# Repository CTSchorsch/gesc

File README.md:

# gesc
DC Motor Controler based on Benjamin Vedders VESC(TM)

Round shape, fits into a DPV tube.
48V (13s), max 60A, needs cooling

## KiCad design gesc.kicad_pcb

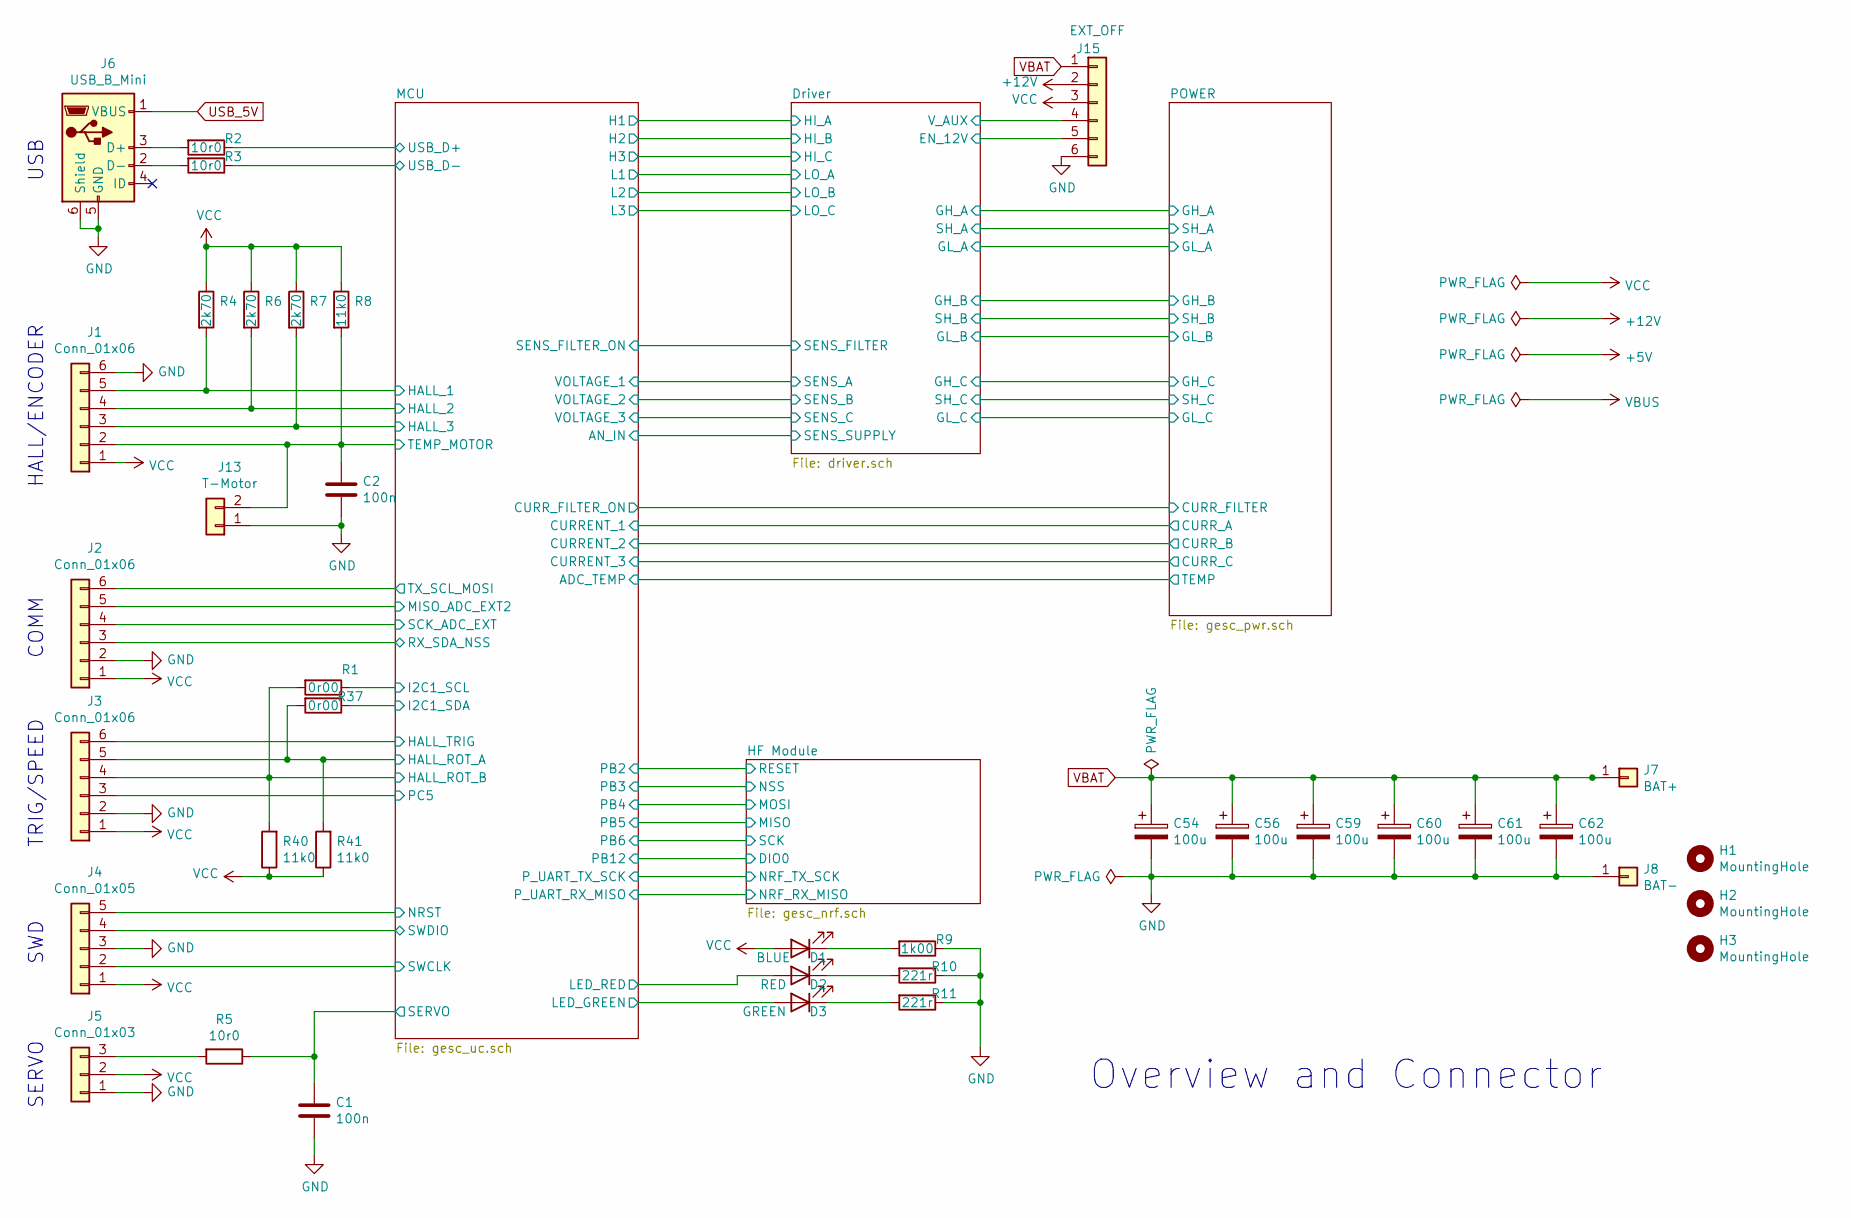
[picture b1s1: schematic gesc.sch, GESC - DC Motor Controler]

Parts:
C1, C2: 100n; C_0805_2012Metric
C54, C56, C59, C60, C61, C62: 100u; CP_Elec_10x10
D1: BLUE; LED_0805_2012Metric
D2: RED; LED_0805_2012Metric
D3: GREEN; LED_0805_2012Metric
H1, H2, H3: MountingHole; MountingHole_3.2mm_M3
J1, J2, J3: Conn_01x06; JST_SH_BM06B-SRSS-TB_1x06-1MP_P1.00mm_Vertical
J4: Conn_01x05; PinHeader_1x05_P2.54mm_Vertical
J5: Conn_01x03; JST_SH_BM03B-SRSS-TB_1x03-1MP_P1.00mm_Vertical
J6: USB_B_Mini; USB_Micro-B_Wuerth_614105150721_Vertical_CircularHoles
J7: BAT+; TestPoint_Pad_5.0x5.0mm
J8: BAT-; TestPoint_Pad_5.0x5.0mm
J13: T-Motor; JST_SH_BM02B-SRSS-TB_1x02-1MP_P1.00mm_Vertical
J15: EXT_OFF; JST_SH_BM06B-SRSS-TB_1x06-1MP_P1.00mm_Vertical
R1, R37: 0r00; R_0805_2012Metric
R2, R3, R5: 10r0; R_0805_2012Metric
R4: 2k70; R_0805_2012Metric; LCSC 1
R6, R7: 2k70; R_0805_2012Metric
R8, R40, R41: 11k0; R_0805_2012Metric
R9: 1k00; R_0805_2012Metric
R10, R11: 221r; R_0805_2012Metric

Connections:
+12V: J15.2; also elsewhere on the board
/Driver/EN_12V: J15.5; also elsewhere on the board
/Driver/V_AUX: J15.4; also elsewhere on the board
/MCU/HALL_1: J1.5, R4.2; also elsewhere on the board
/MCU/HALL_2: J1.4, R6.2; also elsewhere on the board
/MCU/HALL_3: J1.3, R7.2; also elsewhere on the board
/MCU/HALL_ROT_A: J3.5, R37.2, R41.2; also elsewhere on the board
/MCU/HALL_ROT_B: J3.4, R1.2, R40.2; also elsewhere on the board
/MCU/HALL_TRIG: J3.6; also elsewhere on the board
/MCU/I2C1_SCL: R1.1; also elsewhere on the board
/MCU/I2C1_SDA: R37.1; also elsewhere on the board
/MCU/LED_GREEN: D3.2 (A); also elsewhere on the board
/MCU/LED_RED: D2.2 (A); also elsewhere on the board
/MCU/MISO_ADC_EXT2: J2.5; also elsewhere on the board
/MCU/NRST: J4.5; also elsewhere on the board
/MCU/PC5: J3.3; also elsewhere on the board
/MCU/RX_SDA_NSS: J2.3; also elsewhere on the board
/MCU/SCK_ADC_EXT: J2.4; also elsewhere on the board
/MCU/SERVO: C1.1, R5.1; also elsewhere on the board
/MCU/SWCLK: J4.2; also elsewhere on the board
/MCU/SWDIO: J4.4; also elsewhere on the board
/MCU/TEMP_MOTOR: C2.1, J1.2, J13.2, R8.2; also elsewhere on the board
/MCU/TX_SCL_MOSI: J2.6; also elsewhere on the board
/MCU/USB_D+: R2.1; also elsewhere on the board
/MCU/USB_D-: R3.1; also elsewhere on the board
GND: C1.2, C2.2, C54.2, C56.2, C59.2, C60.2, C61.2, C62.2, J1.6, J2.2, J3.2, J4.3, J5.1, J6.5 (GND), J6.6 (Shield), J8.1, J13.1, J15.6, R9.1, R10.1, R11.1; also elsewhere on the board
unnamed: D1.1 (K), R9.2
unnamed: D2.1 (K), R10.2
unnamed: D3.1 (K), R11.2
unnamed: J5.3, R5.2
unnamed: J6.2 (D-), R3.2
unnamed: J6.3 (D+), R2.2
USB_5V: J6.1 (VBUS); also elsewhere on the board
VBAT: C54.1, C56.1, C59.1, C60.1, C61.1, C62.1, J7.1, J15.1; also elsewhere on the board
VCC: D1.2 (A), J1.1, J2.1, J3.1, J4.1, J5.2, J15.3, R4.1, R6.1, R7.1, R8.1, R40.1, R41.1; also elsewhere on the board

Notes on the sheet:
Overview and Connector
USB
HALL/ENCODER
COMM
TRIG/SPEED
SWD
SERVO

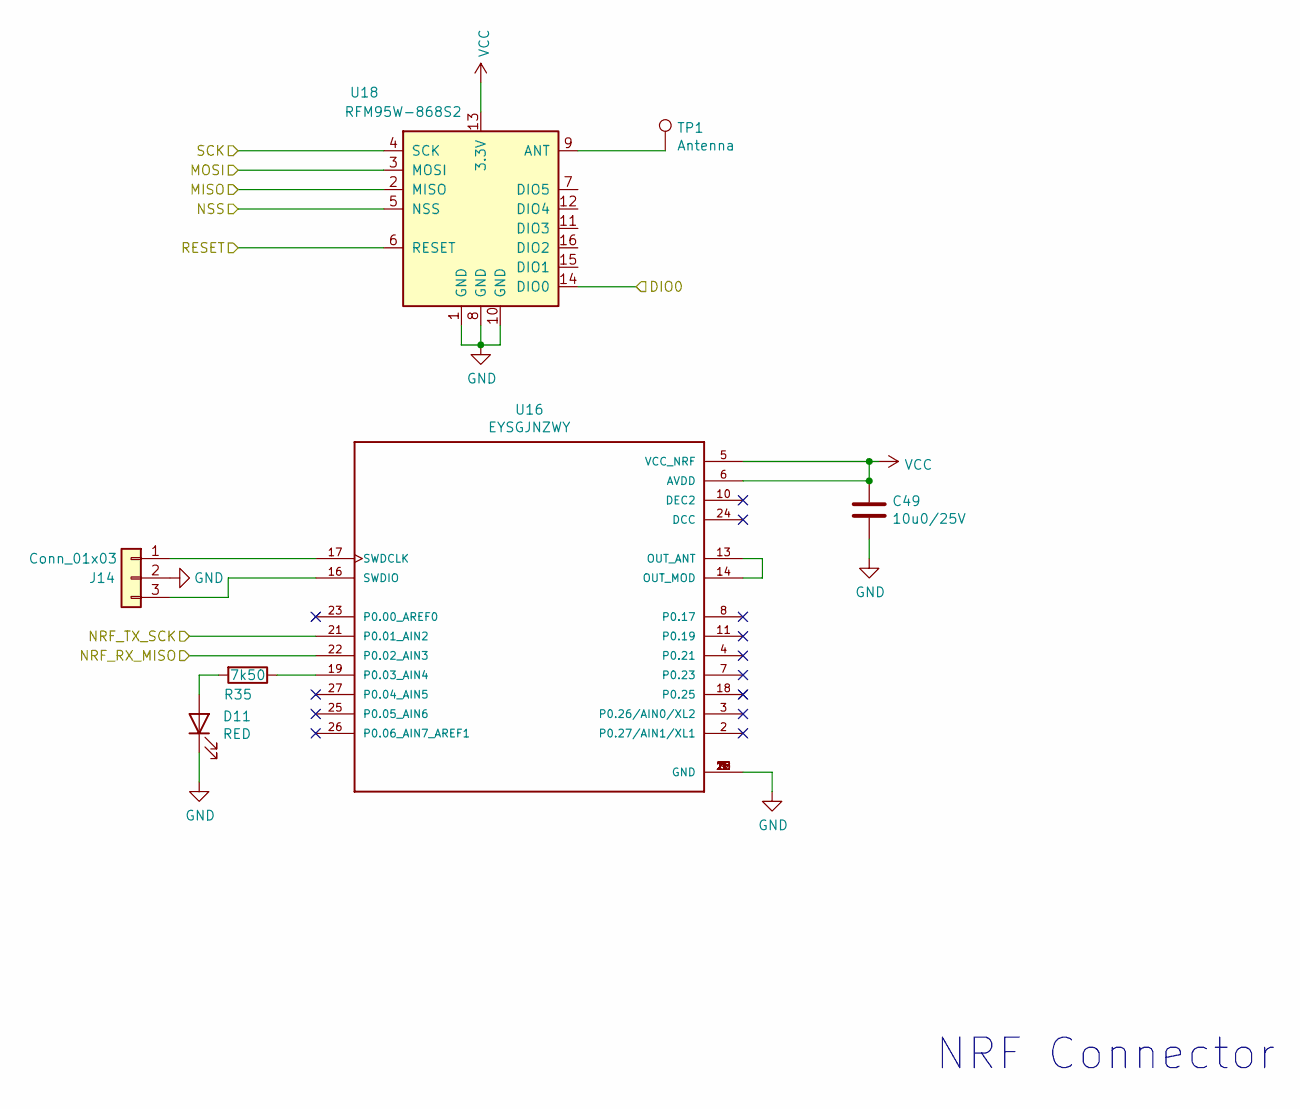
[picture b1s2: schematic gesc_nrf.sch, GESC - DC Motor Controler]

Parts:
C49: 10u0/25V; C_0805_2012Metric
D11: RED; LED_0805_2012Metric
J14: Conn_01x03; PinHeader_1x03_P2.54mm_Vertical
R35: 7k50; R_0805_2012Metric
TP1: Antenna; TestPoint_Pad_D2.0mm
U16: EYSGJNZWY; BLE_EYSGJNZWY
U18: RFM95W-868S2; XCVR_RFM95W-868S2

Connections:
/HF Module/DIO0: U18.14 (DIO0); also elsewhere on the board
/HF Module/MISO: U18.2 (MISO); also elsewhere on the board
/HF Module/MOSI: U18.3 (MOSI); also elsewhere on the board
/HF Module/NRF_RX_MISO: U16.22 (P0.02_AIN3); also elsewhere on the board
/HF Module/NRF_TX_SCK: U16.21 (P0.01_AIN2); also elsewhere on the board
/HF Module/NSS: U18.5 (NSS); also elsewhere on the board
/MCU/PB2: U18.6 (RESET); also elsewhere on the board
/MCU/PB6: U18.4 (SCK); also elsewhere on the board
GND: C49.2, D11.1 (K), J14.2, U16.1 (GND), U16.9 (GND), U16.12 (GND), U16.15 (GND), U16.20 (GND), U16.28 (GND), U18.1 (GND), U18.8 (GND), U18.10 (GND); also elsewhere on the board
unnamed: D11.2 (A), R35.2
unnamed: J14.1, U16.17 (SWDCLK)
unnamed: J14.3, U16.16 (SWDIO)
unnamed: R35.1, U16.19 (P0.03_AIN4)
unnamed 102: TP1.1, U18.9 (ANT); also elsewhere on the board
unnamed: U16.13 (OUT_ANT), U16.14 (OUT_MOD)
VCC: C49.1, U16.5 (VCC_NRF), U16.6 (AVDD), U18.13 (3.3V); also elsewhere on the board

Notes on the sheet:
NRF Connector

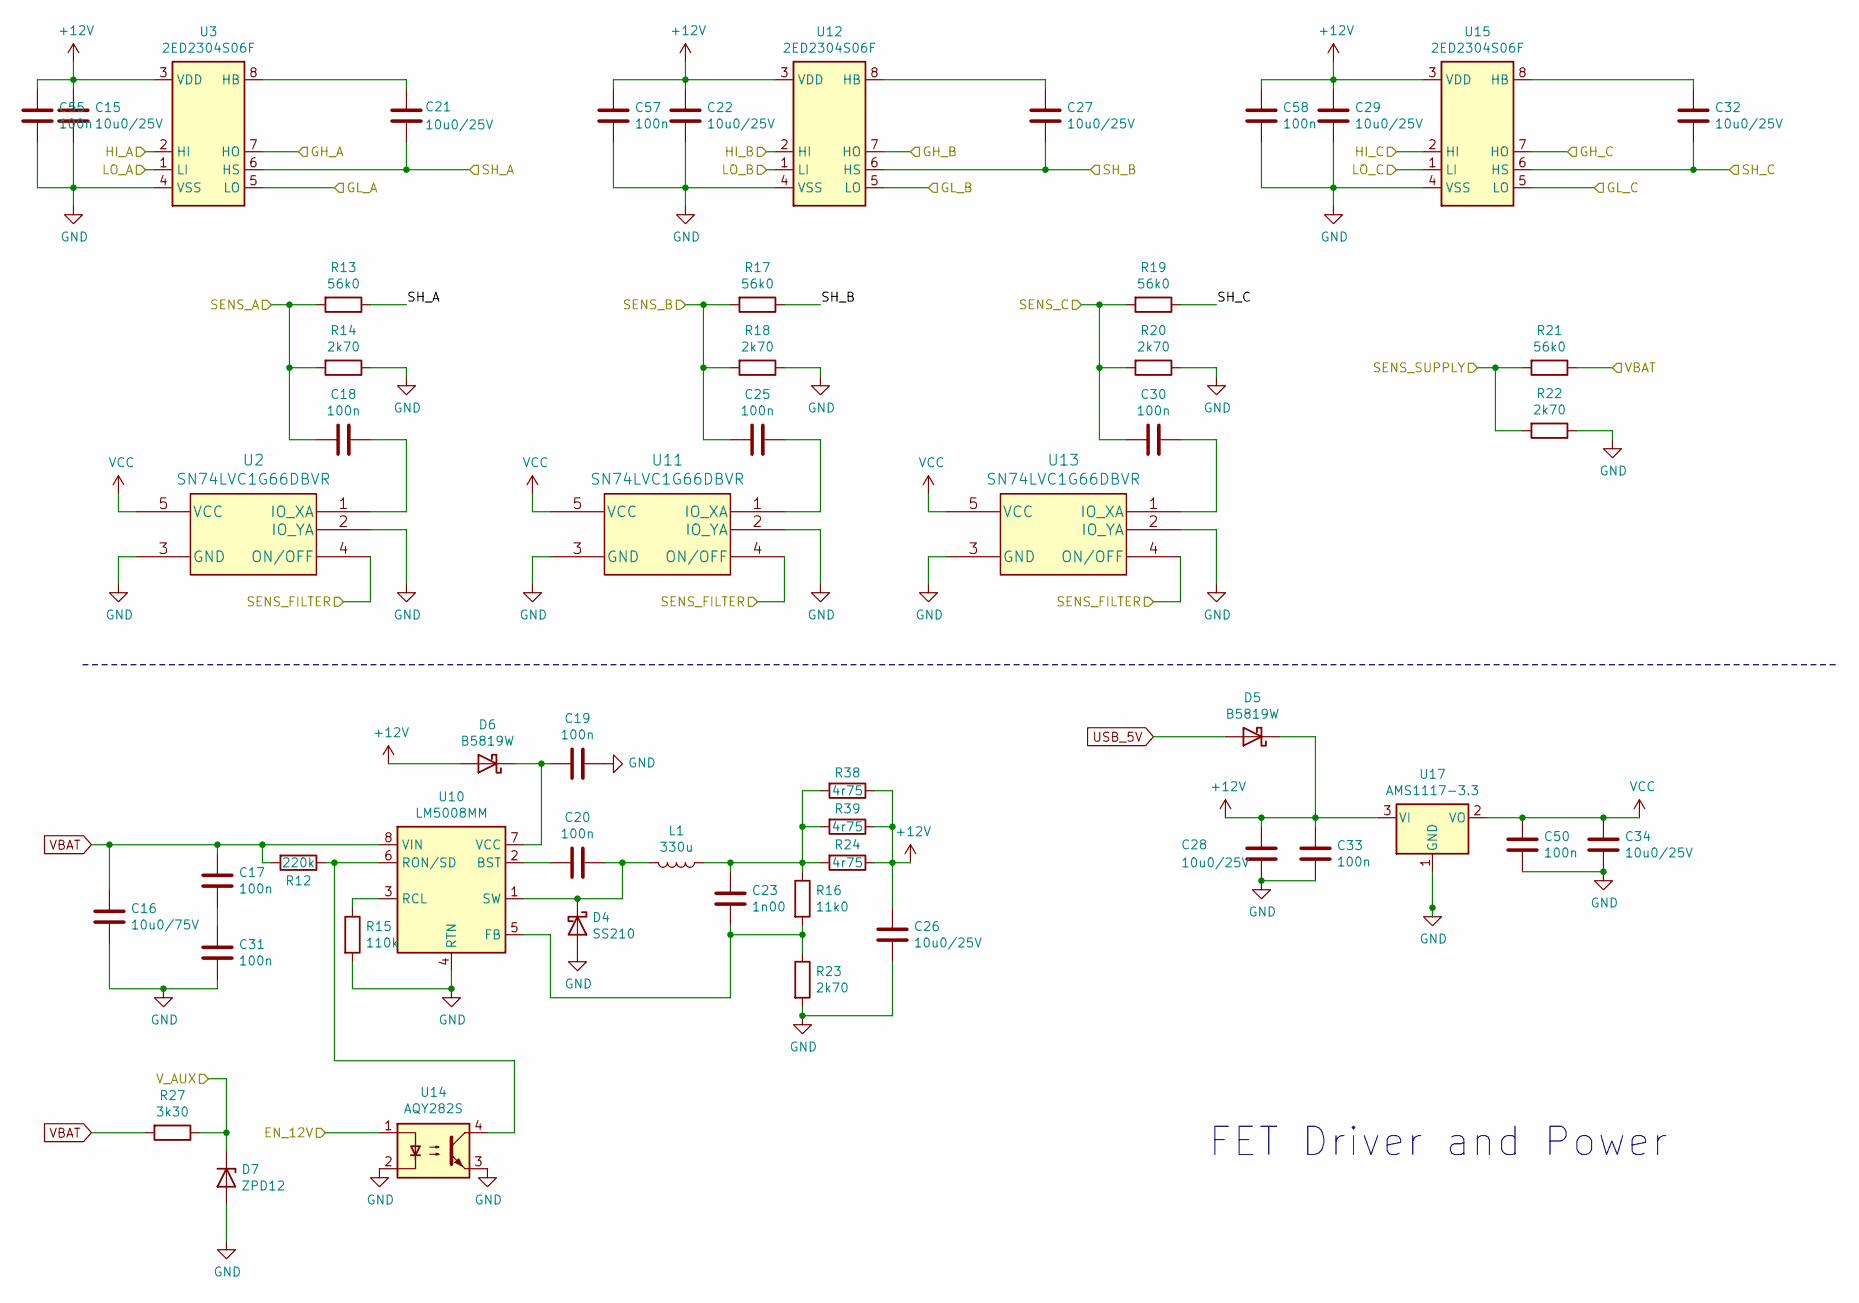
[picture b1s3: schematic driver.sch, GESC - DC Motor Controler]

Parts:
C15, C21, C22, C26, C27, C28, C29, C32, C34: 10u0/25V; C_0805_2012Metric
C16: 10u0/75V; C_1210_3225Metric
C17, C18, C19, C20, C25, C30, C31, C33, C50, C55, C57, C58: 100n; C_0805_2012Metric
C23: 1n00; C_0805_2012Metric
D4: SS210; D_SMA; LCSC C14996
D5, D6: B5819W; D_SOD-123; LCSC C8598
D7: ZPD12; D_MiniMELF
L1: 330u; L_6.3x6.3_H3; Partnumber SWPA6045S331MT; LCSC C83453
R12: 220k; R_0805_2012Metric
R13, R17, R19, R21: 56k0; R_0805_2012Metric
R14, R18, R20, R22, R23: 2k70; R_0805_2012Metric
R15: 110k; R_0805_2012Metric
R16: 11k0; R_0805_2012Metric
R24, R38, R39: 4r75; R_0805_2012Metric
R27: 3k30; R_0805_2012Metric
U2, U11, U13: SN74LVC1G66DBVR; M74VHC1GT66DTT1G; LCSC C133643
U3, U12, U15: 2ED2304S06F; SOIC-8_3.9x4.9mm_P1.27mm
U10: LM5008MM; MSOP-8_3x3mm_P0.65mm; LCSC C9424
U14: AQY282S; SO-4_4.4x4.3mm_P2.54mm; LCSC C250827
U17: AMS1117-3.3; SOT-223-3_TabPin2

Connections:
+12V: C15.1, C22.1, C26.1, C28.1, C29.1, C33.1, C55.1, C57.1, C58.1, D5.1 (K), D6.2 (A), R24.1, R38.1, R39.1, U3.3 (VDD), U12.3 (VDD), U15.3 (VDD), U17.3 (VI); also elsewhere on the board
/Driver/EN_12V: U14.1; also elsewhere on the board
/Driver/GH_A: U3.7 (HO); also elsewhere on the board
/Driver/GH_B: U12.7 (HO); also elsewhere on the board
/Driver/GH_C: U15.7 (HO); also elsewhere on the board
/Driver/GL_A: U3.5 (LO); also elsewhere on the board
/Driver/GL_B: U12.5 (LO); also elsewhere on the board
/Driver/GL_C: U15.5 (LO); also elsewhere on the board
/Driver/SENS_A: C18.2, R13.2, R14.2; also elsewhere on the board
/Driver/SENS_B: C25.2, R17.2, R18.2; also elsewhere on the board
/Driver/SENS_C: C30.2, R19.2, R20.2; also elsewhere on the board
/Driver/SENS_FILTER: U2.4 (ON/OFF), U11.4 (ON/OFF), U13.4 (ON/OFF); also elsewhere on the board
/Driver/SH_A: C21.2, R13.1, U3.6 (HS); also elsewhere on the board
/Driver/SH_B: C27.2, R17.1, U12.6 (HS); also elsewhere on the board
/Driver/SH_C: C32.2, R19.1, U15.6 (HS); also elsewhere on the board
/Driver/V_AUX: D7.1 (K), R27.1; also elsewhere on the board
/MCU/AN_IN: R21.2, R22.2; also elsewhere on the board
/MCU/H1: U3.2 (HI); also elsewhere on the board
/MCU/H2: U12.2 (HI); also elsewhere on the board
/MCU/H3: U15.2 (HI); also elsewhere on the board
/MCU/L1: U3.1 (LI); also elsewhere on the board
/MCU/L2: U12.1 (LI); also elsewhere on the board
/MCU/L3: U15.1 (LI); also elsewhere on the board
GND: C15.2, C16.2, C19.2, C22.2, C26.2, C28.2, C29.2, C31.2, C33.2, C34.2, C50.2, C55.2, C57.2, C58.2, D4.2 (A), D7.2 (A), R14.1, R15.2, R18.1, R20.1, R22.1, R23.2, U2.2 (IO_YA), U2.3 (GND), U3.4 (VSS), U10.4 (RTN), U11.2 (IO_YA), U11.3 (GND), U12.4 (VSS), U13.2 (IO_YA), U13.3 (GND), U14.2, U14.3, U15.4 (VSS), U17.1 (GND); also elsewhere on the board
unnamed: C17.2, C31.1
unnamed: C18.1, U2.1 (IO_XA)
unnamed: C19.1, D6.1 (K), U10.7 (VCC)
unnamed: C20.1, U10.2 (BST)
unnamed: C20.2, D4.1 (K), L1.2, U10.1 (SW)
unnamed: C21.1, U3.8 (HB)
unnamed: C23.1, L1.1, R16.1, R24.2, R38.2, R39.2
unnamed: C23.2, R16.2, R23.1, U10.5 (FB)
unnamed: C25.1, U11.1 (IO_XA)
unnamed: C27.1, U12.8 (HB)
unnamed: C30.1, U13.1 (IO_XA)
unnamed: C32.1, U15.8 (HB)
unnamed: R12.1, U10.6 (RON/SD), U14.4
unnamed: R15.1, U10.3 (RCL)
USB_5V: D5.2 (A); also elsewhere on the board
VBAT: C16.1, C17.1, R12.2, R21.1, R27.2, U10.8 (VIN); also elsewhere on the board
VCC: C34.1, C50.1, U2.5 (VCC), U11.5 (VCC), U13.5 (VCC), U17.2 (VO); also elsewhere on the board

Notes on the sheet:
FET Driver and Power

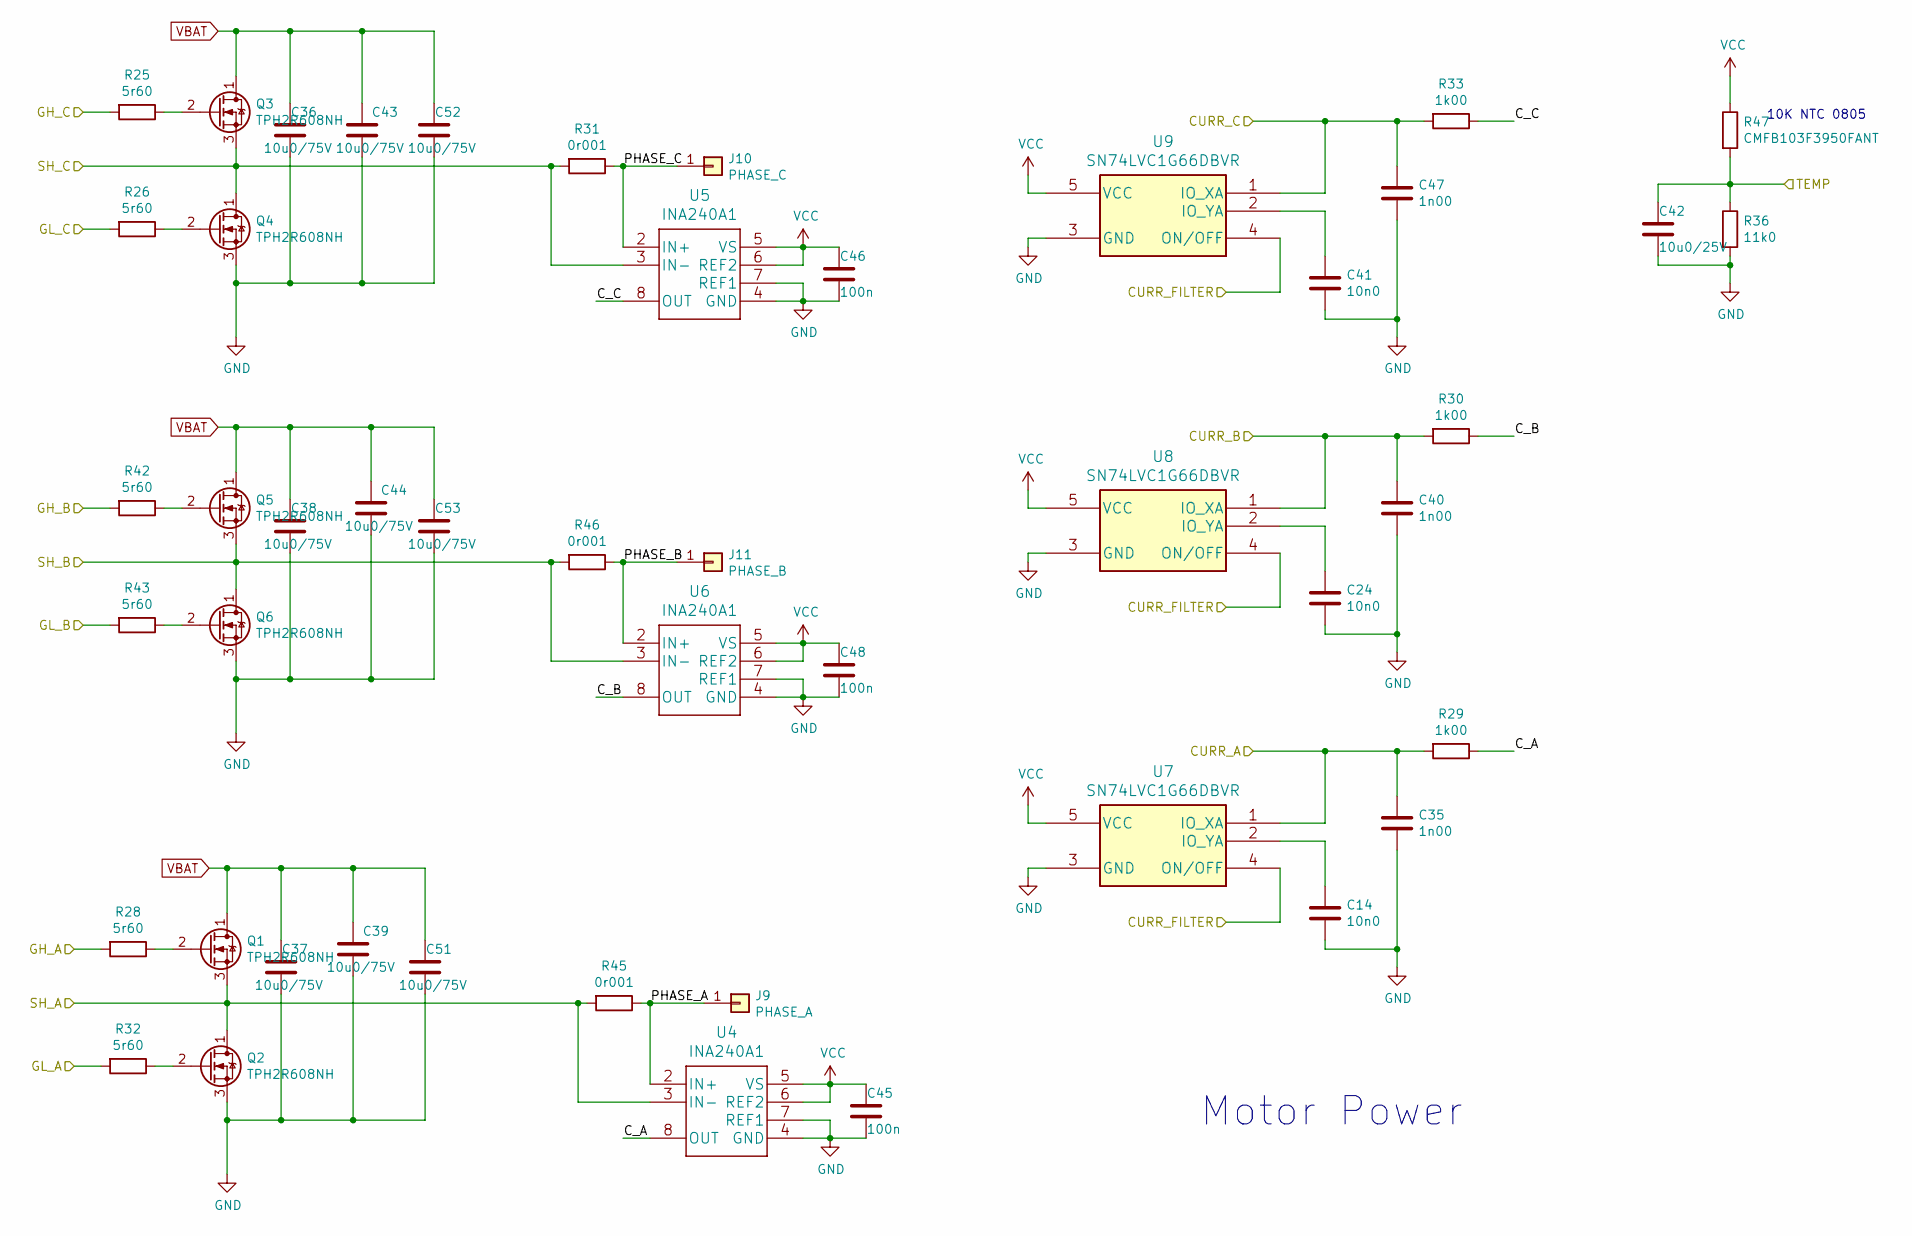
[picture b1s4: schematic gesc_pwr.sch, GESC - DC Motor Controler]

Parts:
C14, C24, C41: 10n0; C_0805_2012Metric
C35, C40, C47: 1n00; C_0805_2012Metric
C36: 10u0/75V; C_1210_3225Metric; LCSC C15850
C37, C38, C39, C43, C44, C51, C52, C53: 10u0/75V; C_1210_3225Metric
C42: 10u0/25V; C_0805_2012Metric
C45, C46, C48: 100n; C_0805_2012Metric
J9: PHASE_A; TestPoint_Pad_5.0x5.0mm
J10: PHASE_C; TestPoint_Pad_5.0x5.0mm
J11: PHASE_B; TestPoint_Pad_5.0x5.0mm
Q1, Q2, Q3, Q4, Q5, Q6: TPH2R608NH; TRANS_TPHR8504PL-3PIN; Partnumber TPH2R608NH; LCSC C146377
R25, R26, R28, R32, R42, R43: 5r60; R_0805_2012Metric
R29, R30, R33: 1k00; R_0805_2012Metric
R31, R45, R46: 0r001; R_2512_6332Metric
R36: 11k0; R_0805_2012Metric
R47: CMFB103F3950FANT; R_0805_2012Metric
U4, U5, U6: INA240A1; INA240A1QPWRQ1; LCSC C93965
U7, U8, U9: SN74LVC1G66DBVR; M74VHC1GT66DTT1G; LCSC C133643

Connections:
/Driver/GH_A: R28.2; also elsewhere on the board
/Driver/GH_B: R42.2; also elsewhere on the board
/Driver/GH_C: R25.2; also elsewhere on the board
/Driver/GL_A: R32.2; also elsewhere on the board
/Driver/GL_B: R43.2; also elsewhere on the board
/Driver/GL_C: R26.2; also elsewhere on the board
/Driver/SH_A: Q1.3 (S), Q2.1 (D), R45.2, U4.3 (IN-); also elsewhere on the board
/Driver/SH_B: Q5.3 (S), Q6.1 (D), R46.2, U6.3 (IN-); also elsewhere on the board
/Driver/SH_C: Q3.3 (S), Q4.1 (D), R31.2, U5.3 (IN-); also elsewhere on the board
/MCU/ADC_TEMP: C42.1, R36.1, R47.2; also elsewhere on the board
/MCU/CURRENT_1: C35.1, R29.2, U7.1 (IO_XA); also elsewhere on the board
/MCU/CURRENT_2: C40.1, R30.2, U8.1 (IO_XA); also elsewhere on the board
/MCU/CURRENT_3: C47.1, R33.2, U9.1 (IO_XA); also elsewhere on the board
/POWER/CURR_FILTER: U7.4 (ON/OFF), U8.4 (ON/OFF), U9.4 (ON/OFF); also elsewhere on the board
/POWER/C_A: R29.1, U4.8 (OUT)
/POWER/C_B: R30.1, U6.8 (OUT)
/POWER/C_C: R33.1, U5.8 (OUT)
/POWER/PHASE_A: J9.1, R45.1, U4.2 (IN+)
/POWER/PHASE_B: J11.1, R46.1, U6.2 (IN+)
/POWER/PHASE_C: J10.1, R31.1, U5.2 (IN+)
GND: C14.2, C24.2, C35.2, C36.2, C37.2, C38.2, C39.2, C40.2, C41.2, C42.2, C43.2, C44.2, C45.2, C46.2, C47.2, C48.2, C51.2, C52.2, C53.2, Q2.3 (S), Q4.3 (S), Q6.3 (S), R36.2, U4.4 (GND), U4.7 (REF1), U5.4 (GND), U5.7 (REF1), U6.4 (GND), U6.7 (REF1), U7.3 (GND), U8.3 (GND), U9.3 (GND); also elsewhere on the board
unnamed: C14.1, U7.2 (IO_YA)
unnamed: C24.1, U8.2 (IO_YA)
unnamed: C41.1, U9.2 (IO_YA)
unnamed: Q1.2 (G), R28.1
unnamed: Q2.2 (G), R32.1
unnamed: Q3.2 (G), R25.1
unnamed: Q4.2 (G), R26.1
unnamed: Q5.2 (G), R42.1
unnamed: Q6.2 (G), R43.1
VBAT: C36.1, C37.1, C38.1, C39.1, C43.1, C44.1, C51.1, C52.1, C53.1, Q1.1 (D), Q3.1 (D), Q5.1 (D); also elsewhere on the board
VCC: C45.1, C46.1, C48.1, R47.1, U4.5 (VS), U4.6 (REF2), U5.5 (VS), U5.6 (REF2), U6.5 (VS), U6.6 (REF2), U7.5 (VCC), U8.5 (VCC), U9.5 (VCC); also elsewhere on the board

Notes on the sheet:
Motor Power
10K NTC 0805

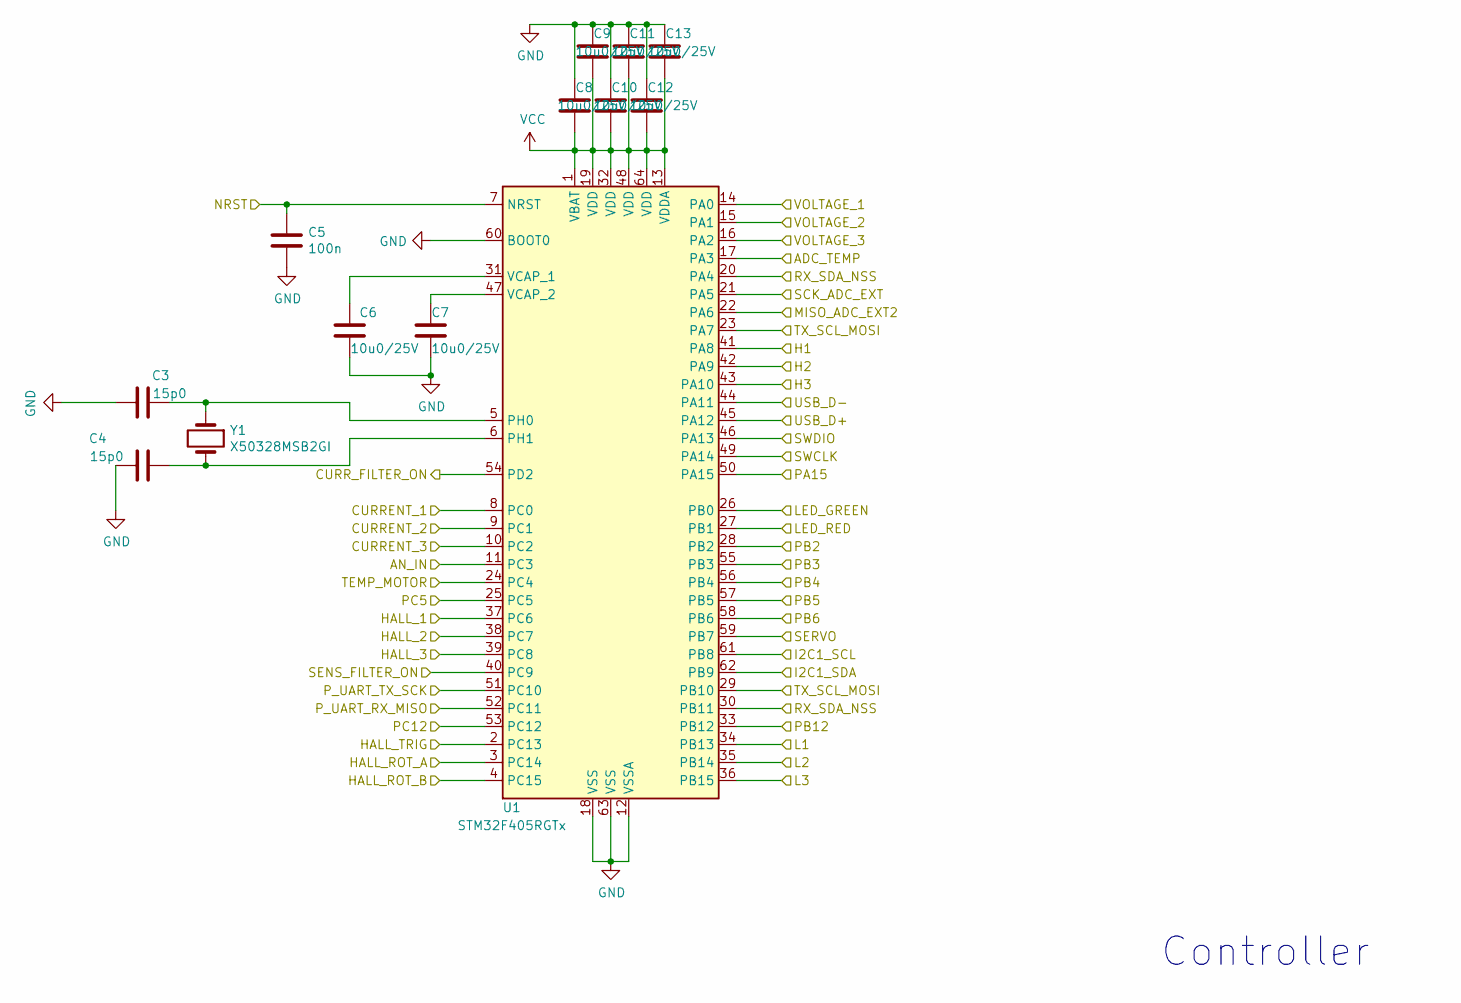
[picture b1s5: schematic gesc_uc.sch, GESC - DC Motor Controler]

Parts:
C3, C4: 15p0; C_0805_2012Metric
C5: 100n; C_0805_2012Metric
C6, C7, C8, C9, C10, C11, C12, C13: 10u0/25V; C_0805_2012Metric
U1: STM32F405RGTx; LQFP-64_10x10mm_P0.5mm; LCSC C15742
Y1: X50328MSB2GI; Crystal_SMD_5032-2Pin_5.0x3.2mm; LCSC C115962

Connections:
/Driver/SENS_A: U1.14 (PA0); also elsewhere on the board
/Driver/SENS_B: U1.15 (PA1); also elsewhere on the board
/Driver/SENS_C: U1.16 (PA2); also elsewhere on the board
/Driver/SENS_FILTER: U1.40 (PC9); also elsewhere on the board
/HF Module/DIO0: U1.33 (PB12); also elsewhere on the board
/HF Module/MISO: U1.57 (PB5); also elsewhere on the board
/HF Module/MOSI: U1.56 (PB4); also elsewhere on the board
/HF Module/NRF_RX_MISO: U1.52 (PC11); also elsewhere on the board
/HF Module/NRF_TX_SCK: U1.51 (PC10); also elsewhere on the board
/HF Module/NSS: U1.55 (PB3); also elsewhere on the board
/MCU/ADC_TEMP: U1.17 (PA3); also elsewhere on the board
/MCU/AN_IN: U1.11 (PC3); also elsewhere on the board
/MCU/CURRENT_1: U1.8 (PC0); also elsewhere on the board
/MCU/CURRENT_2: U1.9 (PC1); also elsewhere on the board
/MCU/CURRENT_3: U1.10 (PC2); also elsewhere on the board
/MCU/H1: U1.41 (PA8); also elsewhere on the board
/MCU/H2: U1.42 (PA9); also elsewhere on the board
/MCU/H3: U1.43 (PA10); also elsewhere on the board
/MCU/HALL_1: U1.37 (PC6); also elsewhere on the board
/MCU/HALL_2: U1.38 (PC7); also elsewhere on the board
/MCU/HALL_3: U1.39 (PC8); also elsewhere on the board
/MCU/HALL_ROT_A: U1.3 (PC14); also elsewhere on the board
/MCU/HALL_ROT_B: U1.4 (PC15); also elsewhere on the board
/MCU/HALL_TRIG: U1.2 (PC13); also elsewhere on the board
/MCU/I2C1_SCL: U1.61 (PB8); also elsewhere on the board
/MCU/I2C1_SDA: U1.62 (PB9); also elsewhere on the board
/MCU/L1: U1.34 (PB13); also elsewhere on the board
/MCU/L2: U1.35 (PB14); also elsewhere on the board
/MCU/L3: U1.36 (PB15); also elsewhere on the board
/MCU/LED_GREEN: U1.26 (PB0); also elsewhere on the board
/MCU/LED_RED: U1.27 (PB1); also elsewhere on the board
/MCU/MISO_ADC_EXT2: U1.22 (PA6); also elsewhere on the board
/MCU/NRST: C5.1, U1.7 (NRST); also elsewhere on the board
/MCU/PB2: U1.28 (PB2); also elsewhere on the board
/MCU/PB6: U1.58 (PB6); also elsewhere on the board
/MCU/PC5: U1.25 (PC5); also elsewhere on the board
/MCU/RX_SDA_NSS: U1.20 (PA4), U1.30 (PB11); also elsewhere on the board
/MCU/SCK_ADC_EXT: U1.21 (PA5); also elsewhere on the board
/MCU/SERVO: U1.59 (PB7); also elsewhere on the board
/MCU/SWCLK: U1.49 (PA14); also elsewhere on the board
/MCU/SWDIO: U1.46 (PA13); also elsewhere on the board
/MCU/TEMP_MOTOR: U1.24 (PC4); also elsewhere on the board
/MCU/TX_SCL_MOSI: U1.23 (PA7), U1.29 (PB10); also elsewhere on the board
/MCU/USB_D+: U1.45 (PA12); also elsewhere on the board
/MCU/USB_D-: U1.44 (PA11); also elsewhere on the board
/POWER/CURR_FILTER: U1.54 (PD2); also elsewhere on the board
GND: C3.2, C4.2, C5.2, C6.1, C7.1, C8.1, C9.1, C10.1, C11.1, C12.1, C13.1, U1.12 (VSSA), U1.18 (VSS), U1.60 (BOOT0), U1.63 (VSS); also elsewhere on the board
unnamed: C3.1, U1.5 (PH0), Y1.1
unnamed: C4.1, U1.6 (PH1), Y1.2
unnamed: C6.2, U1.31 (VCAP_1)
unnamed: C7.2, U1.47 (VCAP_2)
VCC: C8.2, C9.2, C10.2, C11.2, C12.2, C13.2, U1.1 (VBAT), U1.13 (VDDA), U1.19 (VDD), U1.32 (VDD), U1.48 (VDD), U1.64 (VDD); also elsewhere on the board

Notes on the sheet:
Controller

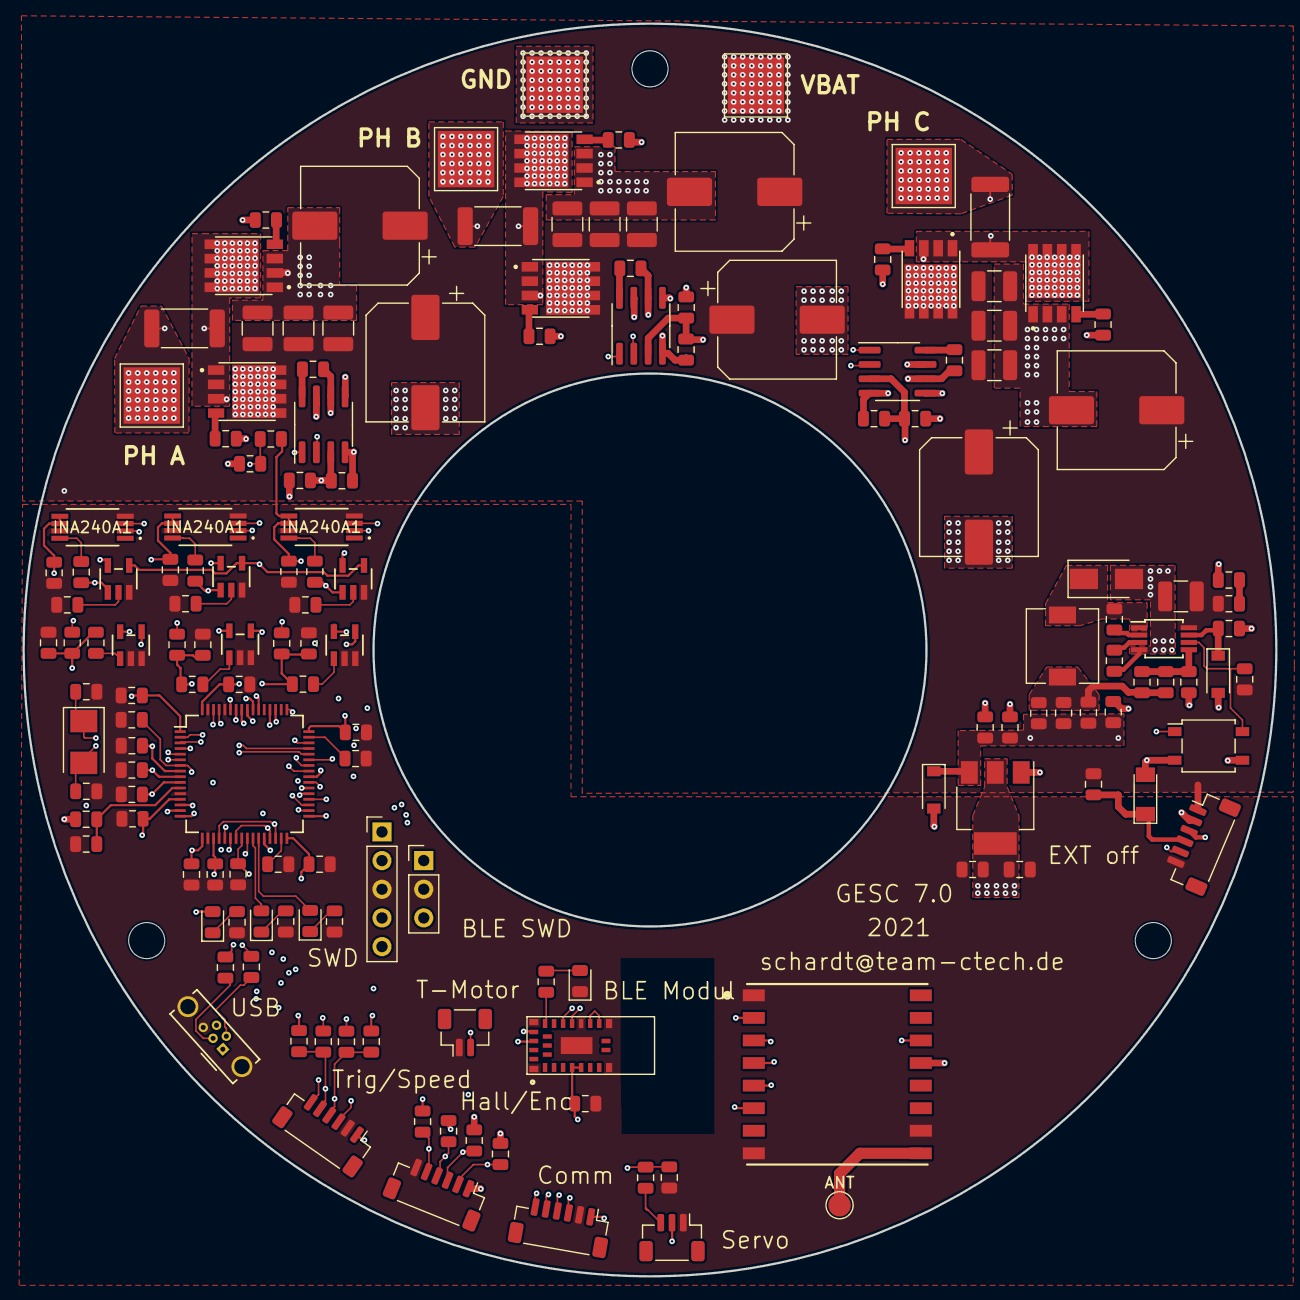
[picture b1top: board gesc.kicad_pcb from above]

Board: 4 copper layers, 111.0 x 111.0 mm, 159 parts (0 on the bottom side), 107 nets.

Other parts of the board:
ANT: Antenna; TestPoint_Pad_D2.0mm

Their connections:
unnamed 102: ANT.1; also elsewhere on the board

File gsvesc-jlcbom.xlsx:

Comment | Designator | Footprint | LCSC Partnumber
100n | C2, C1, C5, C21, C27, C32, C30, C25, C18, C17, C19, C46, C48, C45, | 0805 | C49678
15p0 | C3, C4, | 0805 | C1794
10u0/75V | C16, C36, C43, C38, C44, C37, C39, | 1210 | C13585
10n0 | C20, C23, C31, C14, C24, C41, | 0805 | C1710
22u0/25V | C26, | 0805 | C45783
100u | C33, C34, | CASE-C_6032 | C7171
1n00 | C35, C40, C47, | 0805 | C46653
10u0/25V | C49, C6, C7, C9, C8, C10, C11, C12, C13, C15, C22, C29, C28, C42, | 0805 | C15850
BLUE | D1, | 0805 | C2293
RED | D2, D11, | 0805 | C2293
GREEN | D3, | 0805 | C2297
SS210 | D4, D5, | SMA | C14996
B5819W | D6, D7, | SOD-123 | C8598
SMMBD914LT3G | D8, D10, D9, | SOT-23-3 | C233426
470u | L1, | SMD-PIND-12.5x12.5x6_2.9x5.4 | C169393
15u0 | L2, | SMD-PIND-6.6x7.1x3.0_1.6x3.0 | C132136
TPH2R608NH,L1Q | Q3, Q4, Q5, Q6, Q1, Q2, | SOP-8_EP_5.0x5.0x1.27P | C146377
0R00 | R1, | 0805 | C17477
22R1 | R2, R3, | 0805 | C17561
100R | R5, | 0805 | C17408
2k70 | R6, R7, R4, R22, R20, R18, R14, R23, | 0805 | C17530
10k0 | R8, R16, R36, R37, R40 | 0805 | C17414
1k00 | R9, R29, R30, R33, | 0805 | C17513
221R | R10, R11, | 0805 | C17557
680k | R12, R15, | 0805 | C17772
56k0 | R21, R19, R17, R13, | 0805 | C4382
4R75 | R24, R39, R38, R26, R25, R43, R42, R32, R28, | 0805 | C17675
13k0 | R27, | 0805 | C17455
0R001 | R31, R46, R45, | 2512 | C76233
7k50 | R35, R34, | 0805 | C17807
STM32F405RGTx | U1, | LQFP-64_10x10x05P | C15742
LM5107 | U3, U12, U15, | SOIC-8_3.9x4.9x1.27P | C129332
INA240A2 | U5, U6, U4, | TSSOP-8 | C129949
LM5008MM | U10, | VSSOP-8_3.0x3.0x0.65P | C9424
SN74LVC1G66DBVR | U13, U11, U2, U7, U8, U9, | SOT-23-5 | C133643
TPS5430DDA | U14, | SOP-8_3.9x4.9x1.27P | C9864
EYSGJNZWY | U16,
TMP100NA_250 | U17, | SOT-23-6L | C133806
X50328MSB2GI | Y1, | SMD-4 | C115962

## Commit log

2018-11-28 Moved Project to KiCad
2018-11-28 aufräumen
2018-11-28 revert
2018-11-28 Aufgeräumt Teil 2
2018-11-28 datei wiederhergestellt
2018-12-11 SCM Fertig
2019-01-04 design finished gerber created
2019-01-22 Revision 2.0a
2019-02-19 fix some bugs
2019-02-19 change inverter to npn :)
2019-02-20 add 3d pictures
2019-02-21 BUG: Inrush current force lt1910 to switch off
2019-12-10 GSVESC 2.0
2019-12-13 test
2020-01-29 gsesc v3, work in progress
2020-01-29 lib vergessen
2020-01-29 library wieder im projektordner
2020-02-05 Aufgeräumt
2020-02-06 Umbau auf doppelFET, INA240
2020-02-10 First Version V3 - Change FET to TPH2R506PL - 1oz copper on all layer - switch analog amp to INA240 - remove Elkos - add more ceramic c - separate current measurement tracks from gate driver tracks -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
2020-02-10 Version 3 update - JST as SMD part - move FET tracks
2020-02-11 implement remarks/changes from Alex
2020-02-11 Fertigungsdaten V3.0
2020-04-09 V3 finish, JLC ready
2020-04-10 V4 first version
2020-04-10 5V raus
2020-04-11 Power Supply geändert
2020-04-11 Powersupply geändert
2020-04-20 V4 pre
2020-04-20 V4 alpha
2020-04-21 Add boot-diode to use LM5109A as alternative FET driver
2020-04-21 einige Bauteile geändert, so dass sie Basic Parts bei JLC sind
2020-04-21 BLE Modul hinzugefügt, optional
2020-04-28 V4 before review
2020-05-01 small changes
2020-05-02 Planes und Vias
2020-05-04 fertig gerouted
2020-05-04 Ready for JLC
2020-05-26 some bug fixes for next pcb-run
    - Add JST connector for Motor Temp
    - Remove USB 5V
    - add correct footprint for D8,9,10
    - add JST connector for external off
2020-05-26 clean up
2020-05-26 add BUGS.txt again
2020-05-27 BUG Fixes, see BUGS.txt
2020-06-02 bug fixing
2020-08-01 add PDF
2020-08-03 hw 4 freeze
2020-08-03 add bugs to BUGS.txt
2020-08-05 temp
2020-08-08 pre review
2020-08-10 review
2020-08-10 Apply Feedback from Martin:
    - Add more GND Vias to lowside FET
    - use "power GND" for driver
2020-08-10 some more vias
2020-08-10 add picture
2020-08-11 change Caps
2020-09-02 HW5 ready
2020-10-04 bugfix
2020-10-19 current range too small, fix with new Shunt Resistor
    !! better: use ina240A1
2021-01-08 Add Pull ups for i2c change shunt
2021-01-23 save
2021-01-25 PCB updated: - reroute SH_X - change 3V3 Power supply - add VBUS to 3V3 regulator - use LM5107 - change Layer/Plane assignment - move current sense tracks to layer 2
2021-01-25 - remove solder-mask from bottom layer
2021-01-27 - add separate connection between lowside source and driver
2021-02-02 JLC ready
2021-02-04 new schematic export
2021-02-18 BUGS ergänzt
2021-02-19 |--- Add Schottky between phase and gnd at HS pin of LM5107 |--- Add 5R6 in phase line to HS pin of LM5107 |--- Change high side bypass cap to 10u/25V |--- Add 14V TVS diode parallel to high side byp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
2021-02-26 Version mit UCC27211
2021-03-04 - new driver 2ED2304S06F - separat Elkos for each phase - new FET placement
2021-03-06 Version rund platziert
2021-08-29 V7 PCB order
2021-12-03 small fixes
2022-01-03 add new 3d picture

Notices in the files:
parts and their libraries:
Copyright 2016 Accelerated Designs. All rights reserved.
